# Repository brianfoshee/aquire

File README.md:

## Turn your Raspberry Pi into a scientific grade hydroponic/aquaponic monitoring system!

### Hardware
- Raspberry Pi A+
- Raspberry Pi Supported Wifi Card
- Printed Circuit Board
  - BNC Right Angle PCB Mount
  - 100k SMD Resistor
  - 2x20 Pin 2.54mm Double Row Female Pin Header
  - 1x3 pins 2.54mm Female Header Straight (X2)
  - Atlas PH Circuit (Set to i2c mode)
  - Atlas EC Circuit (Set to i2c mode)
  - PH Probe (Atlas or another that uses BNC connector)
  - EC Probe (Atlas or another that uses BNC connector)
  - DS18B20 Waterproof Digital Temperature Sensor

### Firmware
- Written in Go 
- Communicates with Atlas Sceintic chips via I2C and DS18B20 via 1-wire
- Readings are transmitted via UDP to Statsd/Graphite for data storage and reporting

### Weatherproof Case (3D Printable)
- http://www.thingiverse.com/thing:1463063

### Viewing your data
- Once your device is online, send Brian or Nathan a private message and we'll provide you with a link to view your data

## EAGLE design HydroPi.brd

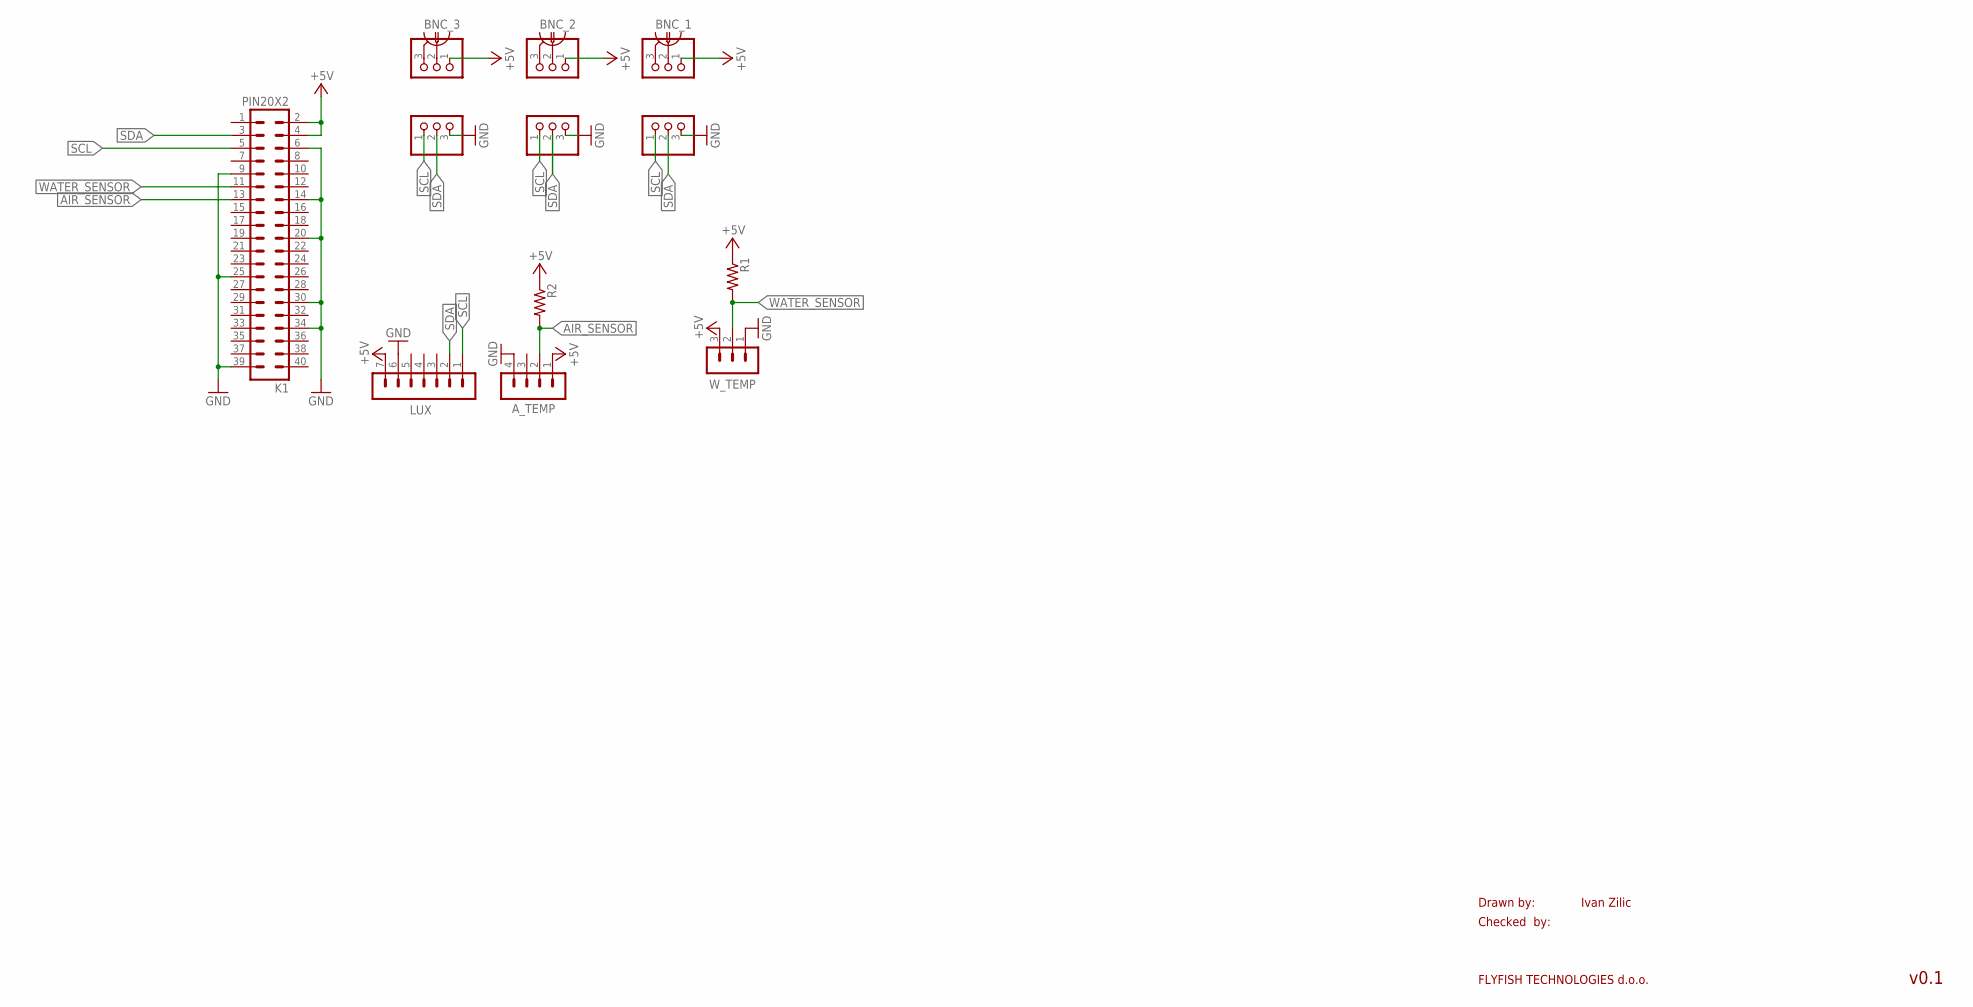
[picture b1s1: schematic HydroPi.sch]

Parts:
A_TEMP: MA04-1
BNC_1, BNC_2, BNC_3: 1-227161-0; AMP_227161
JP1, JP2, JP3, JP4, JP5, JP6: PINHD-1X3; 1X03
K1: PIN20X2; PIN_20X2
LUX: MA07-1
R1, R2: R-US_R0805; R0805
W_TEMP: MA03-1

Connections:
+5V: A_TEMP.1, JP1.1, JP2.1, JP5.1, K1.2, K1.4, LUX.7, R1.1, R2.1, W_TEMP.3
AIR_SENSOR: A_TEMP.2, K1.13, R2.2
GND: A_TEMP.4, JP3.3, JP4.3, JP6.3, K1.6, K1.9, K1.14, K1.20, K1.25, K1.30, K1.34, K1.39, LUX.6, W_TEMP.1
unnamed: BNC_1.1, JP1.2
unnamed: BNC_1.2, JP1.3
unnamed: BNC_2.1, JP2.2
unnamed: BNC_2.2, JP2.3
unnamed: BNC_3.1, JP5.2
unnamed: BNC_3.2, JP5.3
SCL: JP3.1, JP4.1, JP6.1, K1.5, LUX.1
SDA: JP3.2, JP4.2, JP6.2, K1.3, LUX.2
WATER_SENSOR: K1.11, R1.2, W_TEMP.2

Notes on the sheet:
Drawn by:
Checked by:
FLYFISH TECHNOLOGIES d.o.o.
Ivan Zilic
v0.1

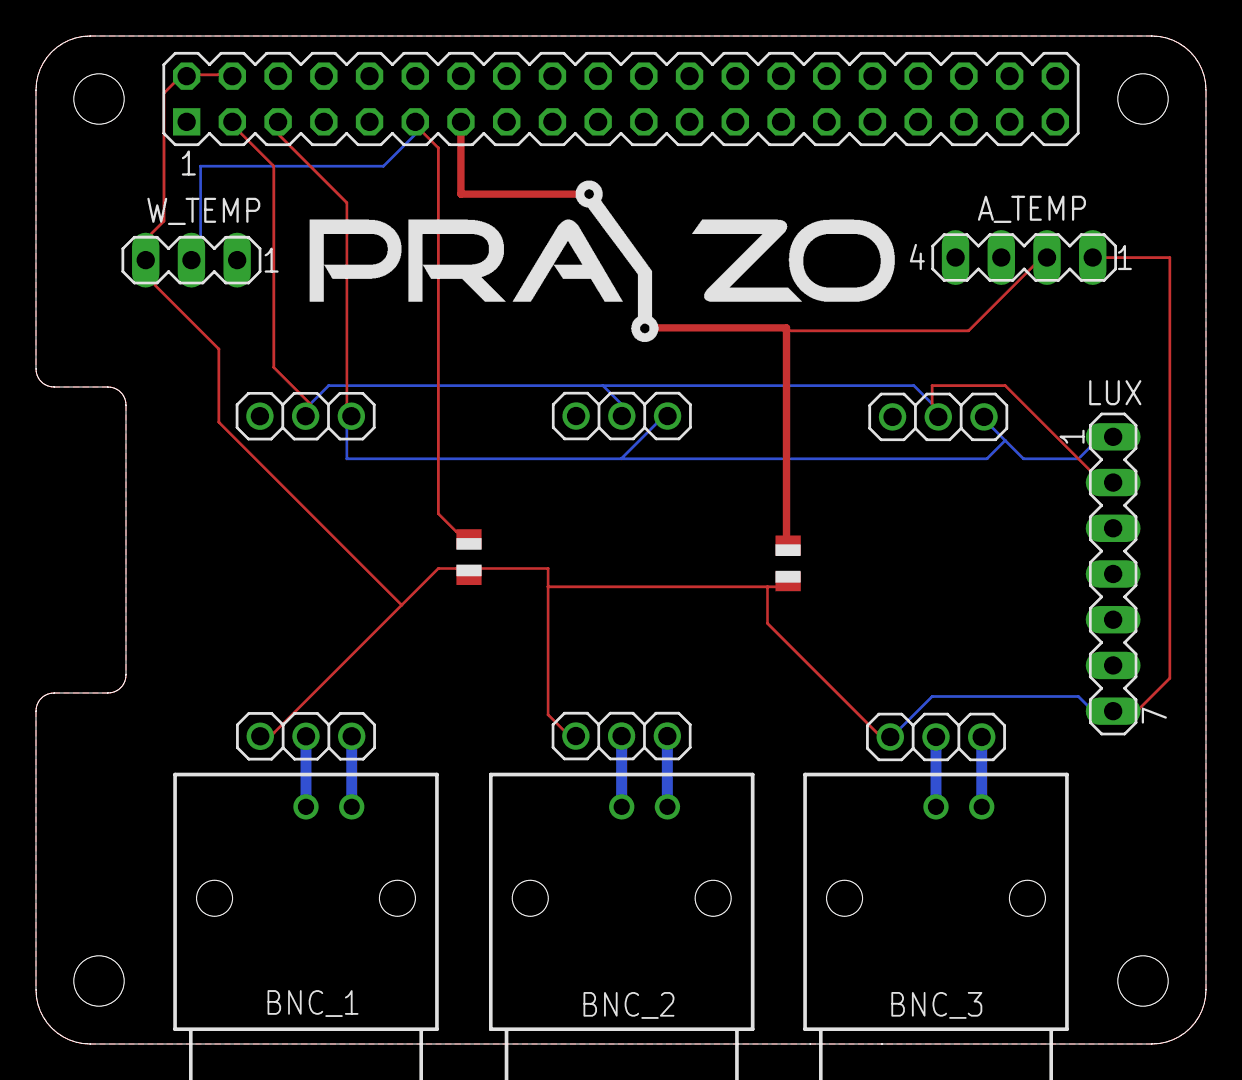
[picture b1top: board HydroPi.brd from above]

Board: 2 copper layers, 65.0 x 56.0 mm, 15 parts (0 on the bottom side), 12 nets.

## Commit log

2015-03-22 Add functions for gathering data and posting to server
2015-04-15 Temperature Dependent Readings, Calibration Functions
2015-04-23 Made I2C handles persistent
2015-04-25 Now uses atlas package
2015-04-25 Updated repo to use brianfoshee instead of crakalakin
2015-04-28 go fmt and goimports
2015-04-28 Improved error handling
2015-04-28 Removed unnecessary comments
2016-03-23 move atlas into atlas package/dir
2016-03-23 update import path
2016-03-24 push to statsd
2016-03-24 Added support for unique device identifier, solves issue #1
2016-04-03 Refactored ph calibration function to make it more extensible and robust. Fixes #2
2016-04-03 Provides CLI for calibrating atlas chips, only PH currently implemented. Solves issue#3
2016-04-08 swap out statsd package. closes #7
2016-04-10 PCB Design Files
2016-04-21 Added files via upload
2016-06-26 Resolves issue 10
2016-06-26 ran gofmt
2016-06-26 Resolves #8 - Added logging
2016-06-26 Resolved issue #11 - 1wire sensor id now dynamic
2016-06-26 Resolves #12 - fixed potential index out of bound when determining 1wire id
2016-06-26 Issue #12 - Removed debugging output unintentionally introduced last commit
2016-06-27 Resolves #13 - Moved onewire connection outside of infinite loop
